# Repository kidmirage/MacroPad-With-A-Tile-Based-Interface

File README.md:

# MacroPad-With-A-Tile-Based-Interface
Repository to hold the software and design files for a MacroPad project that uses tiles to assign predefined macros to specific keys.

For details see: https://hackaday.io/project/192937-a-tile-based-macropad

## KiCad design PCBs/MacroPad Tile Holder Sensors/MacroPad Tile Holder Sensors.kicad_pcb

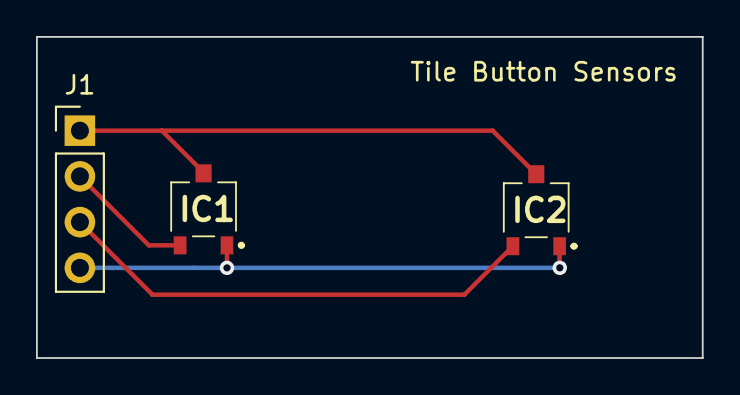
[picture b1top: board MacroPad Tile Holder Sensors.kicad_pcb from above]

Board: 2 copper layers, 37.0 x 17.8 mm, 3 parts (0 on the bottom side), 4 nets.

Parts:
IC1, IC2: EQ430L
J1: Conn_01x04; PinHeader_1x04_P2.54mm_Vertical

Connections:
unnamed: IC1.2 (GND), IC2.2 (GND), J1.GND (Pin_1)
unnamed: IC1.3 (OUT), J1.S1 (Pin_2)
unnamed: IC1.1 (VCC), IC2.1 (VCC), J1.VCC (Pin_4)
unnamed: IC2.3 (OUT), J1.S2 (Pin_3)

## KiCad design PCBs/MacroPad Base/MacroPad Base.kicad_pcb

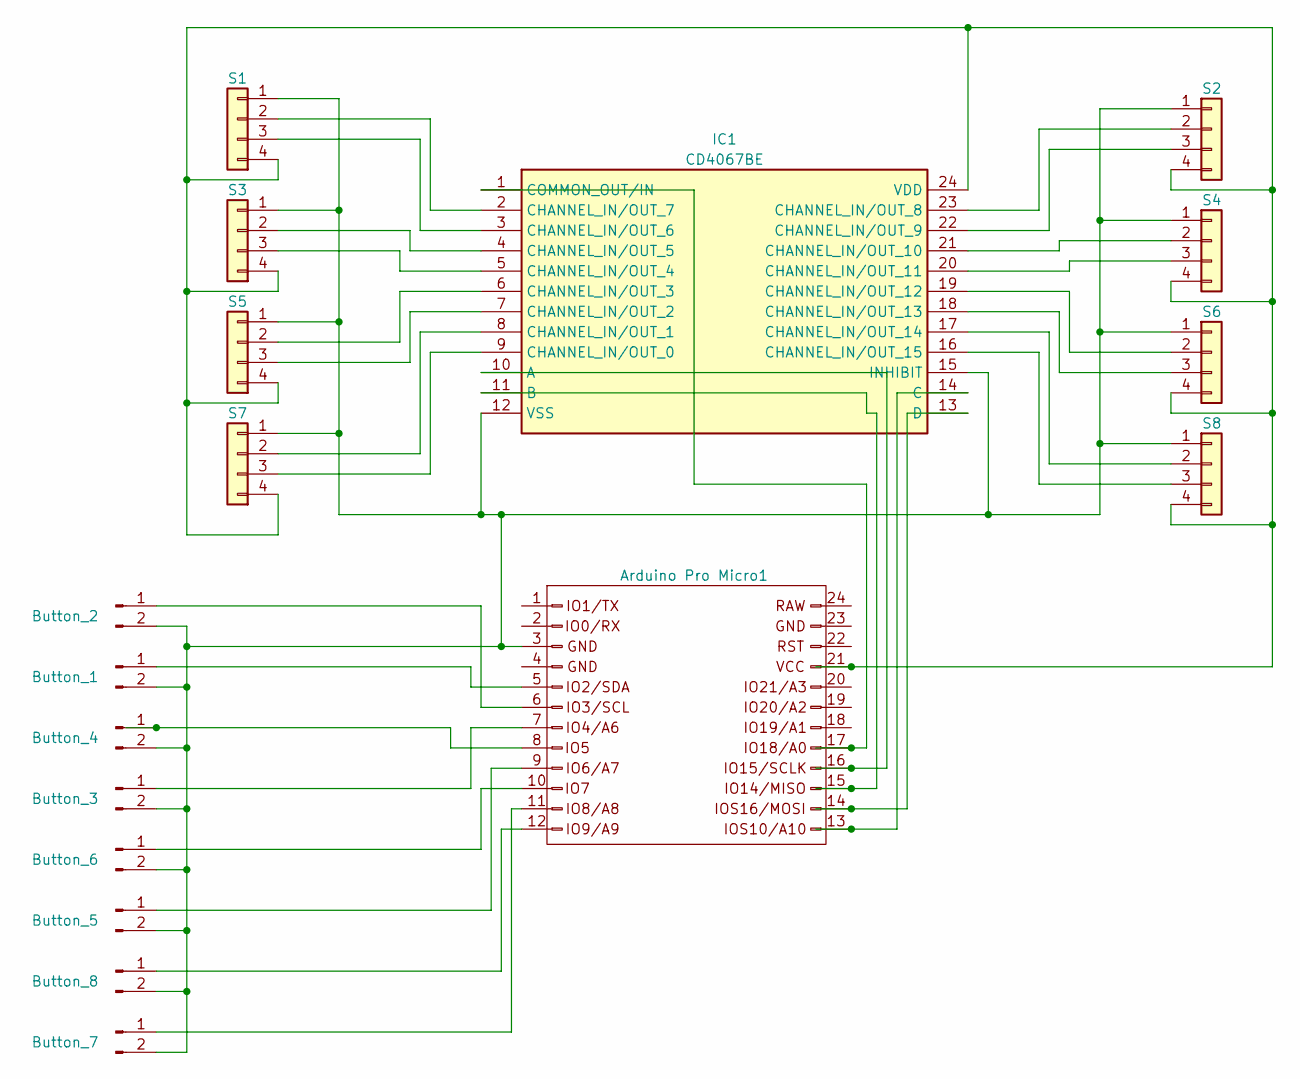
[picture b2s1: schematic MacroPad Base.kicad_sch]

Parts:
Arduino Pro Micro1: Conn_02x12_Counter_Clockwise; DIP-24_W15.24mm
IC1: CD4067BE; DIP1542W56P254L3175H491Q24N; Manufacturer_Part_Number CD4067BE; Mouser Part Number 595-CD4067BE
J1: S3; PinHeader_1x04_P2.54mm_Vertical
J2: Button_2; Key_MX
J3: Button_1; Key_MX
J4: Button_4; Key_MX
J5: Button_3; Key_MX
J6: Button_6; Key_MX
J7: Button_5; Key_MX
J8: Button_8; Key_MX
J9: Button_7; Key_MX
J10: S5; PinHeader_1x04_P2.54mm_Vertical
J11: S7; PinHeader_1x04_P2.54mm_Vertical
J12: S2; PinHeader_1x04_P2.54mm_Vertical
J13: S1; PinHeader_1x04_P2.54mm_Vertical
J14: S4; PinHeader_1x04_P2.54mm_Vertical
J15: S6; PinHeader_1x04_P2.54mm_Vertical
J16: S8; PinHeader_1x04_P2.54mm_Vertical

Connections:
unnamed: Arduino Pro Micro1.3, IC1.12 (VSS), IC1.15 (INHIBIT), J1.1 (Pin_4), J2.2, J3.2, J4.2, J5.2, J6.2, J7.2, J8.2, J9.2, J10.1 (Pin_4), J11.1 (Pin_4), J12.1, J13.1 (Pin_4), J14.1, J15.1, J16.1
unnamed: Arduino Pro Micro1.5, J3.1
unnamed: Arduino Pro Micro1.6, J2.1
unnamed: Arduino Pro Micro1.7, J5.1
unnamed: Arduino Pro Micro1.8, J4.1
unnamed: Arduino Pro Micro1.9, J7.1
unnamed: Arduino Pro Micro1.10, J6.1
unnamed: Arduino Pro Micro1.11, J9.1
unnamed: Arduino Pro Micro1.12, J8.1
unnamed: Arduino Pro Micro1.13, IC1.14 (C)
unnamed: Arduino Pro Micro1.14, IC1.13 (D)
unnamed: Arduino Pro Micro1.15, IC1.11 (B)
unnamed: Arduino Pro Micro1.16, IC1.10 (A)
unnamed: Arduino Pro Micro1.17, IC1.1 (COMMON_OUT/IN)
unnamed: Arduino Pro Micro1.21, IC1.24 (VDD), J1.4 (Pin_1), J10.4 (Pin_1), J11.4 (Pin_1), J12.4, J13.4 (Pin_1), J14.4, J15.4, J16.4
unnamed: IC1.9 (CHANNEL_IN/OUT_0), J11.3 (Pin_2)
unnamed: IC1.8 (CHANNEL_IN/OUT_1), J11.2 (Pin_3)
unnamed: IC1.7 (CHANNEL_IN/OUT_2), J10.3 (Pin_2)
unnamed: IC1.6 (CHANNEL_IN/OUT_3), J10.2 (Pin_3)
unnamed: IC1.5 (CHANNEL_IN/OUT_4), J1.3 (Pin_2)
unnamed: IC1.4 (CHANNEL_IN/OUT_5), J1.2 (Pin_3)
unnamed: IC1.3 (CHANNEL_IN/OUT_6), J13.3 (Pin_2)
unnamed: IC1.2 (CHANNEL_IN/OUT_7), J13.2 (Pin_3)
unnamed: IC1.23 (CHANNEL_IN/OUT_8), J12.2
unnamed: IC1.22 (CHANNEL_IN/OUT_9), J12.3
unnamed: IC1.21 (CHANNEL_IN/OUT_10), J14.2
unnamed: IC1.20 (CHANNEL_IN/OUT_11), J14.3
unnamed: IC1.19 (CHANNEL_IN/OUT_12), J15.2
unnamed: IC1.18 (CHANNEL_IN/OUT_13), J15.3
unnamed: IC1.17 (CHANNEL_IN/OUT_14), J16.2
unnamed: IC1.16 (CHANNEL_IN/OUT_15), J16.3

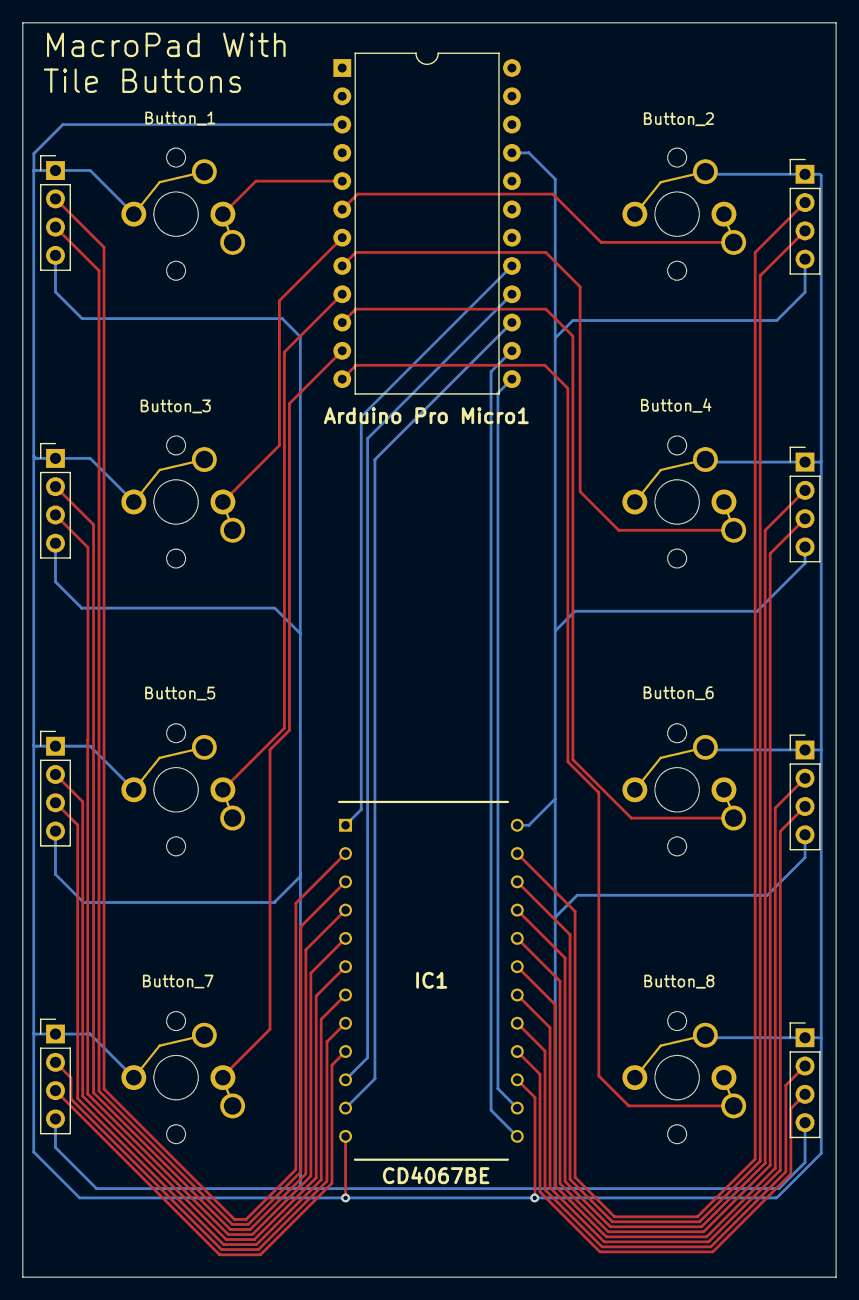
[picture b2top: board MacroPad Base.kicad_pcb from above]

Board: 2 copper layers, 73.0 x 112.7 mm, 18 parts (0 on the bottom side), 31 nets.

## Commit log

2023-10-02 Update README.md
    Added link to Hachaday project.
2023-10-02 Create MacroPad.ino
    First version of the MacroPad firmware.
2023-10-03 Update MacroPad.ino
    Switched from the Keyboard library to the HID-Project library for keyboard support.
2023-10-03 Update MacroPad.ino
    Added comments around macro creation.
2023-10-03 Update MacroPad.ino
    Tweaked comments.
2023-10-03 Update MacroPad.ino
    Fixed missing code.
2023-10-04 Update MacroPad.ino
    Added auto repeat for macro keys.
2023-10-04 Update MacroPad.ino
    Auto repeat start after 2 seconds.
2023-10-05 Update MacroPad.ino
    Better tile selection code.
2023-10-05 Create Calibrate_MacroPad
    Initial version of the Calibrate_MacroPad sketch.
2023-10-05 Create test
2023-10-05 Add files via upload
    Added the model files used to create the MacroPad.
2023-10-05 Delete models/test
    Cleanup.
2023-10-05 Rename Calibrate_MacroPad to Calibrate_MacroPad.ino
    Added extension.
2023-10-20 Add files via upload
    Calibrate for the MacroPad with Tile Buttons.
2023-10-20 Add files via upload
    Firmware for the MacroPad With Tile Buttons. Slightly different than the other macropad because the wiring is different.
2023-10-20 Delete models/Tile Tops.3mf
    Replacing with updated models.
2023-10-20 Delete models directory
    Replacing with updated models.
2023-10-20 Create models
    Create models folder.
2023-10-20 Rename models to test
2023-10-20 Add files via upload
    Updated with latest models.
2023-10-25 Add files via upload
    Added PCBs for MacroPad 3.
